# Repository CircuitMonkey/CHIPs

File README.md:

# CHIPs (aka CHIPz)

CHIPz modules are sub-circuits cooked down into a SMT module with a Cyberpunk Tech aesthetic.

The edge contacts are castelated and resemble the edge of a postage stamp.  Like similar modules on the market, CHIPs are designed to be soldered to a larger PCB board.  One advantage of the CHIPz modules is that a design can be revised or re-engineered to improve a larger design without having to redesign the whole system.  CHIPz also makes it convenient to pre-build smaller modules with common or repetive functions and use them over and over in other larger designs.

Almost all of the numbered designs were designed in EagleCAD and were intended to be sold into the hobby electronics market.  Alas, I have given up on that dream, but offer these designs for anyone who wishes to use them or just study the things I have made over the years. My current and future designs are now made with KiCAD.

I still design CHIPz modules and other things, but not for the purpose of manufacturing or selling.  I use the modules in my own creations and wish to share those things for anyone who has a similar need or wishes to simply understand the workings of these things.

If you wish to simply make a module, you can generally upload the Eagle BRD or KiCAD_PCB file directly to [OSH Park PCB](https://OSHPark.com) for preview and fabrication.

Everyting here is open source with minimal (if at all) license requirements.  Copy, mash-up and use to your hearts content.

## NOTE
New designs will be placed in a sub-directory, like [Synth] is.  Older designs will be moved eventually into a sub-folder but for now will dominate the file listing you see.

Enjoy,

Mark Koch  (Circuit Monkey)

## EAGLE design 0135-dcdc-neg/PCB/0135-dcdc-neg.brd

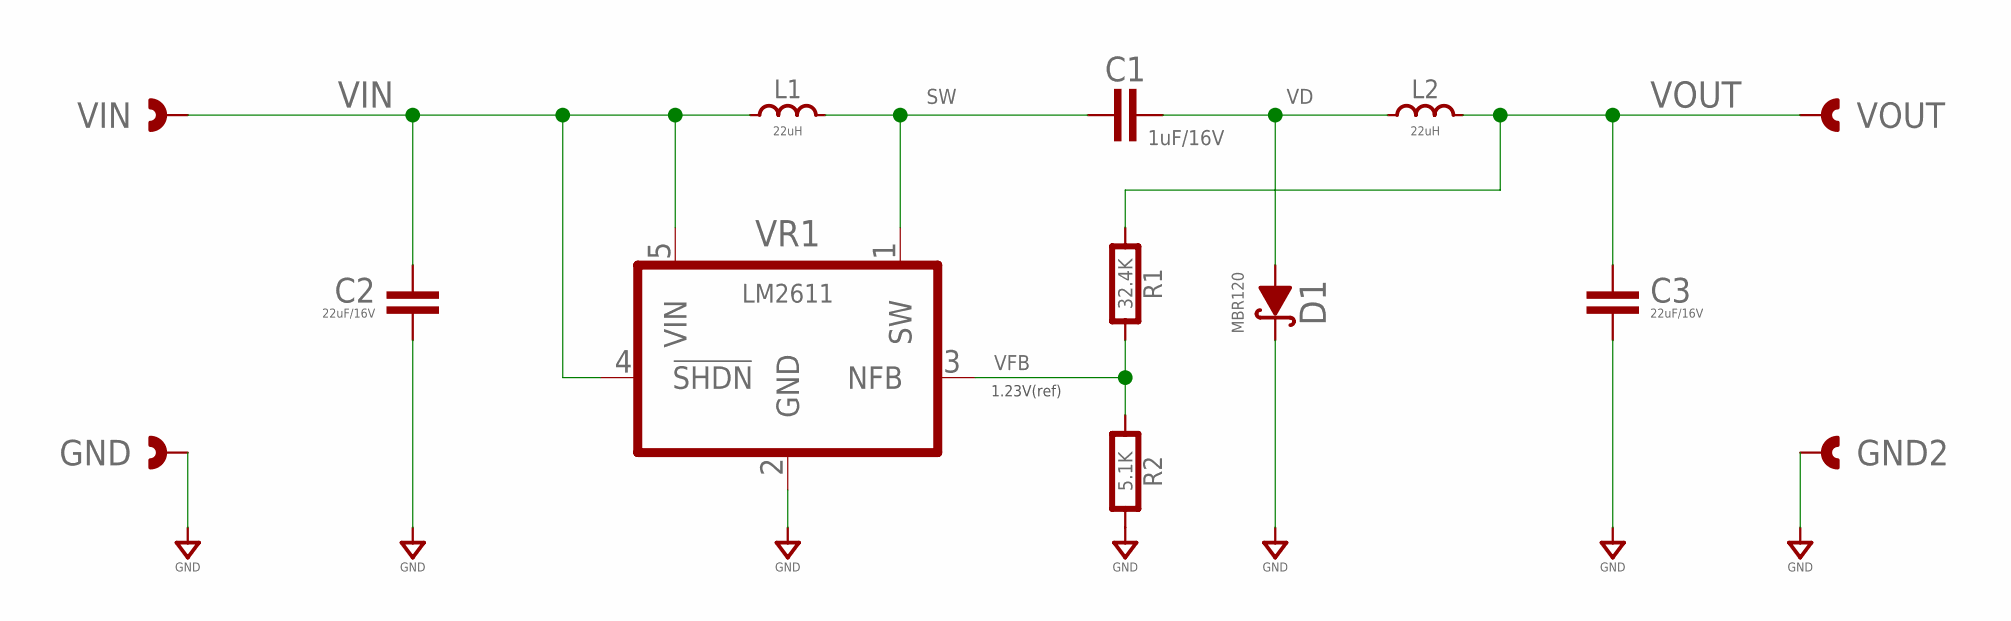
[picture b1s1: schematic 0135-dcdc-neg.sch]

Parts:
C1: 1uF/16V; 0603-CAP
C2, C3: 22uF/16V; 1210-CAP
D1: MBR120; SOD-123
GND, GND2: CAST-01X12.00MM; CAST01-2.00MM
L1, L2: 22uH; IND-MU8400
R1: 32.4K; 0603-RES
R2: 5.1K; 0603-RES
VIN: CAST-01X12.00MM; CAST01-2.00MM
VOUT: CAST-01X12.00MM; CAST01-2.00MM
VR1: LM2611; SOT-23-5

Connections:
GND: C2.2, C3.2, D1.K, GND.1, GND.P$1, GND.P$2, GND2.1, GND2.P$1, GND2.P$2, R2.2, VR1.2 (GND)
SW: C1.1, L1.1, VR1.1 (SW)
VD: C1.2, D1.A, L2.2
VFB: R1.2, R2.1, VR1.3 (NFB)
VIN: C2.1, L1.2, VIN.1, VIN.P$1, VIN.P$2, VR1.4 (!SHDN), VR1.5 (VIN)
VOUT: C3.1, L2.1, R1.1, VOUT.1, VOUT.P$1, VOUT.P$2

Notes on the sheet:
1.23V(ref)

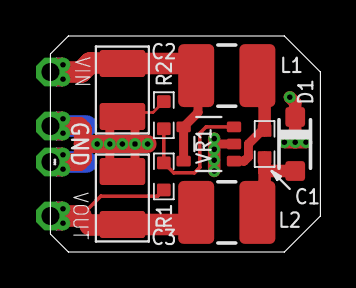
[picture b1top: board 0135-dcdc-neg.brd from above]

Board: 2 copper layers, 15.0 x 12.0 mm, 13 parts (0 on the bottom side), 6 nets.

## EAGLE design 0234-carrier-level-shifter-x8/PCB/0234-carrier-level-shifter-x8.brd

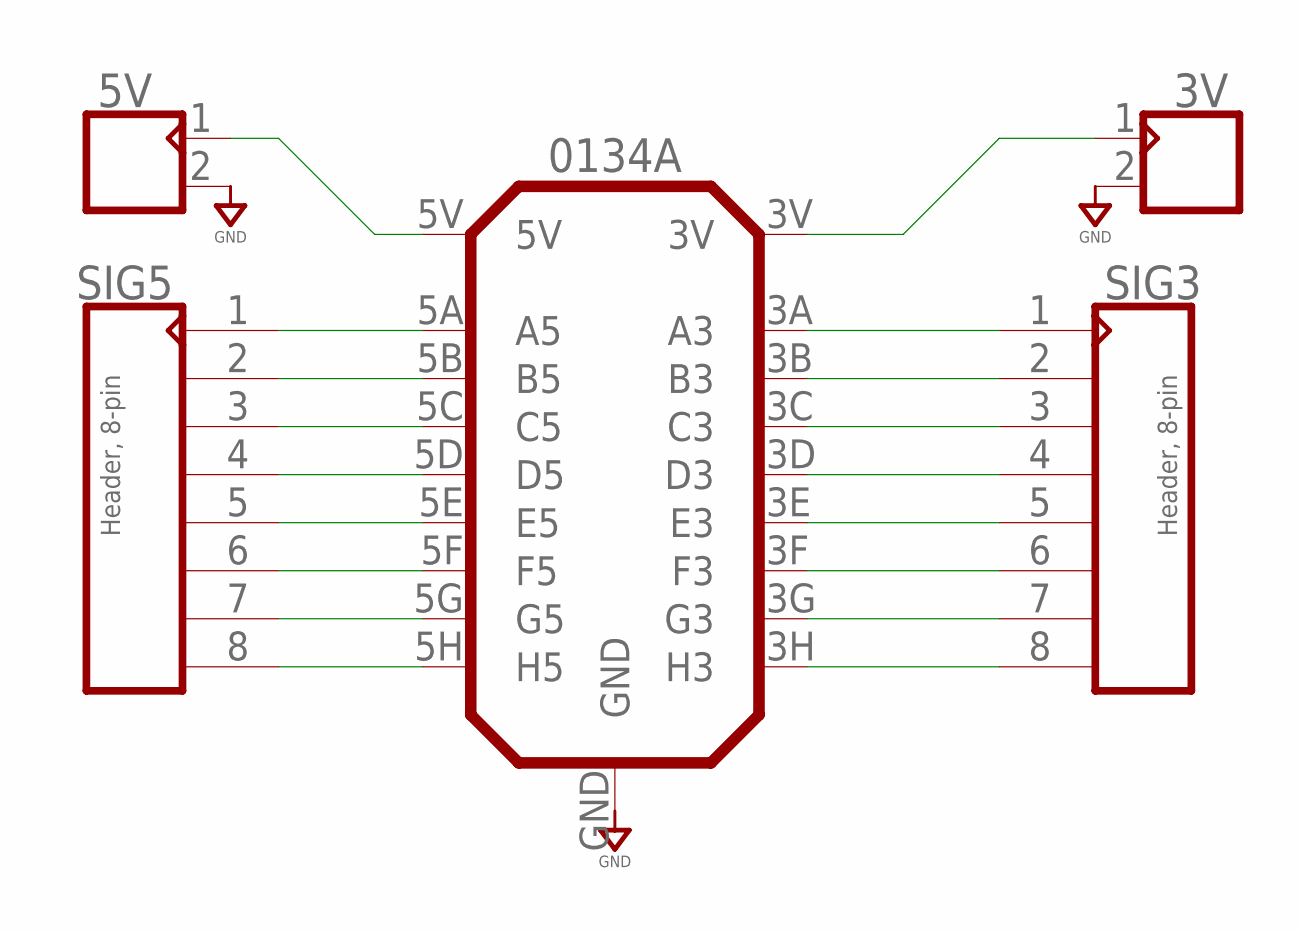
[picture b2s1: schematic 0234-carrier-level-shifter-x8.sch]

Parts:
3V, 5V: CON_02X1-2.54MM-THD-VT; MA02X1-VT-THD
0134A: 0134REV_A; 0134A
SIG3, SIG5: Header, 8-pin; MA08X1-VT-THD

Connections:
GND: 3V.2, 5V.2, 0134A.GND
unnamed: 5V.1, 0134A.5V
unnamed: 3V.1, 0134A.3V
unnamed: 0134A.5F (F5), SIG5.6
unnamed: 0134A.5E (E5), SIG5.5
unnamed: 0134A.5D (D5), SIG5.4
unnamed: 0134A.5C (C5), SIG5.3
unnamed: 0134A.5B (B5), SIG5.2
unnamed: 0134A.5A (A5), SIG5.1
unnamed: 0134A.5G (G5), SIG5.7
unnamed: 0134A.5H (H5), SIG5.8
unnamed: 0134A.3F (F3), SIG3.6
unnamed: 0134A.3E (E3), SIG3.5
unnamed: 0134A.3D (D3), SIG3.4
unnamed: 0134A.3C (C3), SIG3.3
unnamed: 0134A.3B (B3), SIG3.2
unnamed: 0134A.3A (A3), SIG3.1
unnamed: 0134A.3G (G3), SIG3.7
unnamed: 0134A.3H (H3), SIG3.8

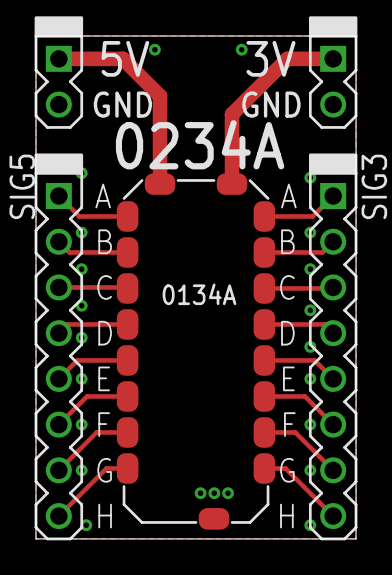
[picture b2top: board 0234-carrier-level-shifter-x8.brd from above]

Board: 2 copper layers, 17.8 x 27.9 mm, 5 parts (0 on the bottom side), 19 nets.

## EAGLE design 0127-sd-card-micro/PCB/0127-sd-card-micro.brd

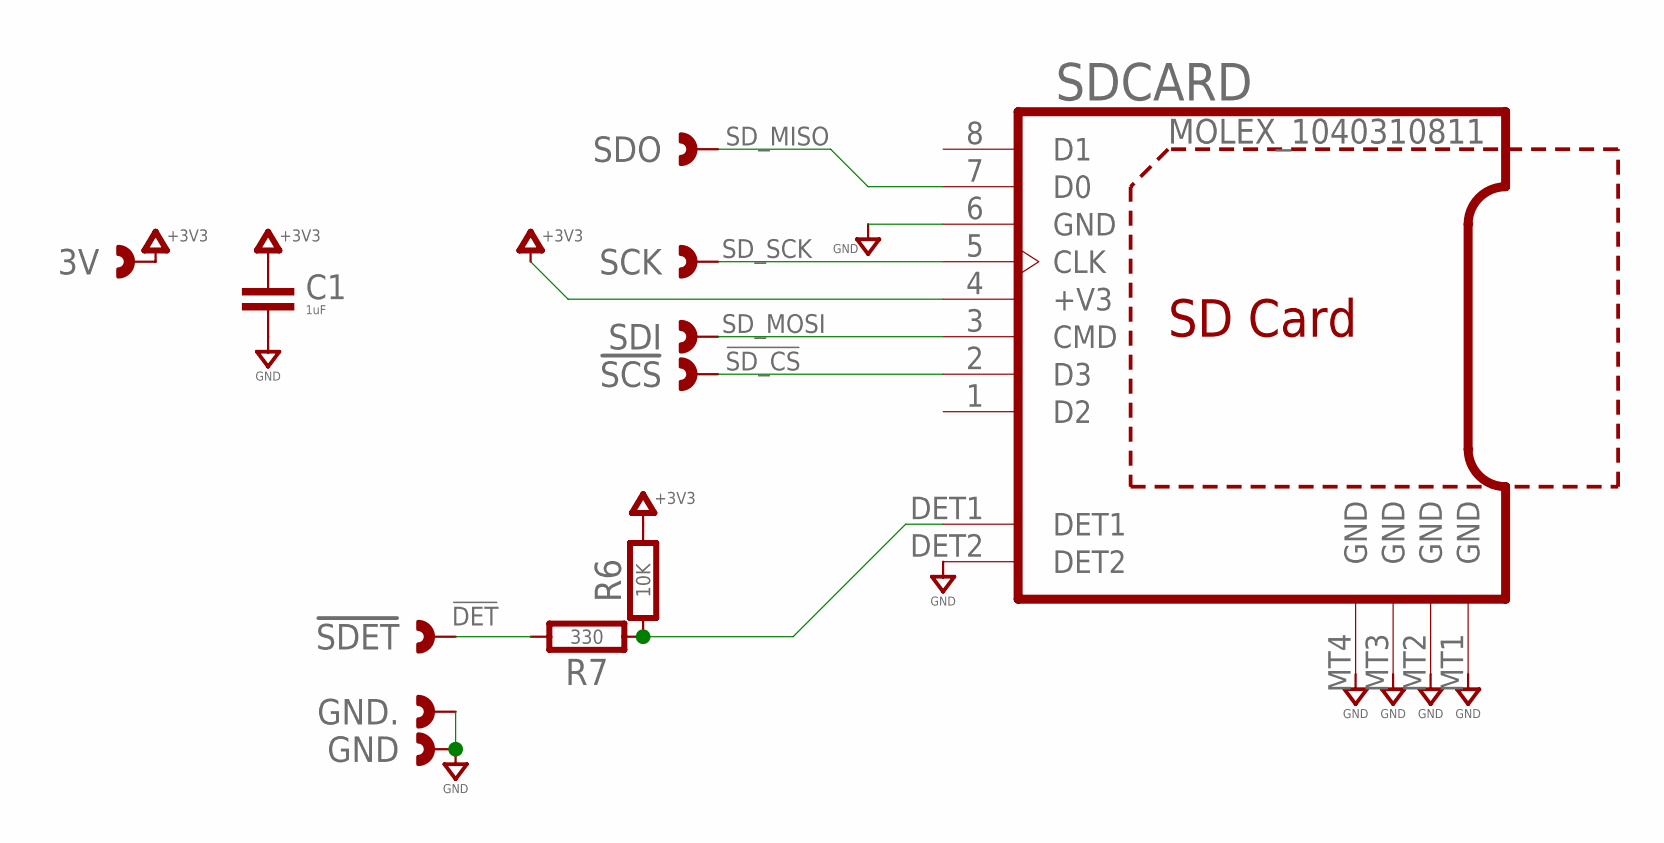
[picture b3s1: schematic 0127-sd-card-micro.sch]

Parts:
3V: CAST-01X12.00MM; CAST01-2.00MM
!SCS: CAST-01X12.00MM; CAST01-2.00MM
!SDET: CAST-01X12.00MM; CAST01-2.00MM
C1: 1uF; 0603-CAP
GND, GND.: CAST-01X12.00MM; CAST01-2.00MM
R6: 10K; 0603-RES
R7: 330; 0603-RES
SCK: CAST-01X12.00MM; CAST01-2.00MM
SDCARD: MOLEX_1040310811; MOLEX_1040310811_USD
SDI: CAST-01X12.00MM; CAST01-2.00MM
SDO: CAST-01X12.00MM; CAST01-2.00MM

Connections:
!DET: !SDET.1, !SDET.P$1, !SDET.P$2, R7.2
!SD_CS: !SCS.1, !SCS.P$1, !SCS.P$2, SDCARD.2 (D3)
!SD_DET: R6.1, R7.1, SDCARD.DET1
+3V3: 3V.1, 3V.P$1, 3V.P$2, C1.1, R6.2, SDCARD.4 (+V3)
GND: C1.2, GND.1, GND.P$1, GND.P$2, GND..1, GND..P$1, GND..P$2, SDCARD.6 (GND), SDCARD.DET2, SDCARD.MT1 (GND), SDCARD.MT2 (GND), SDCARD.MT3 (GND), SDCARD.MT4 (GND)
SD_MISO: SDCARD.7 (D0), SDO.1, SDO.P$1, SDO.P$2
SD_MOSI: SDCARD.3 (CMD), SDI.1, SDI.P$1, SDI.P$2
SD_SCK: SCK.1, SCK.P$1, SCK.P$2, SDCARD.5 (CLK)

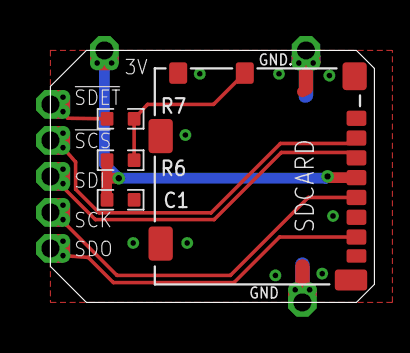
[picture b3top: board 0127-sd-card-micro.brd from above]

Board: 2 copper layers, 18.0 x 14.0 mm, 12 parts (0 on the bottom side), 8 nets.

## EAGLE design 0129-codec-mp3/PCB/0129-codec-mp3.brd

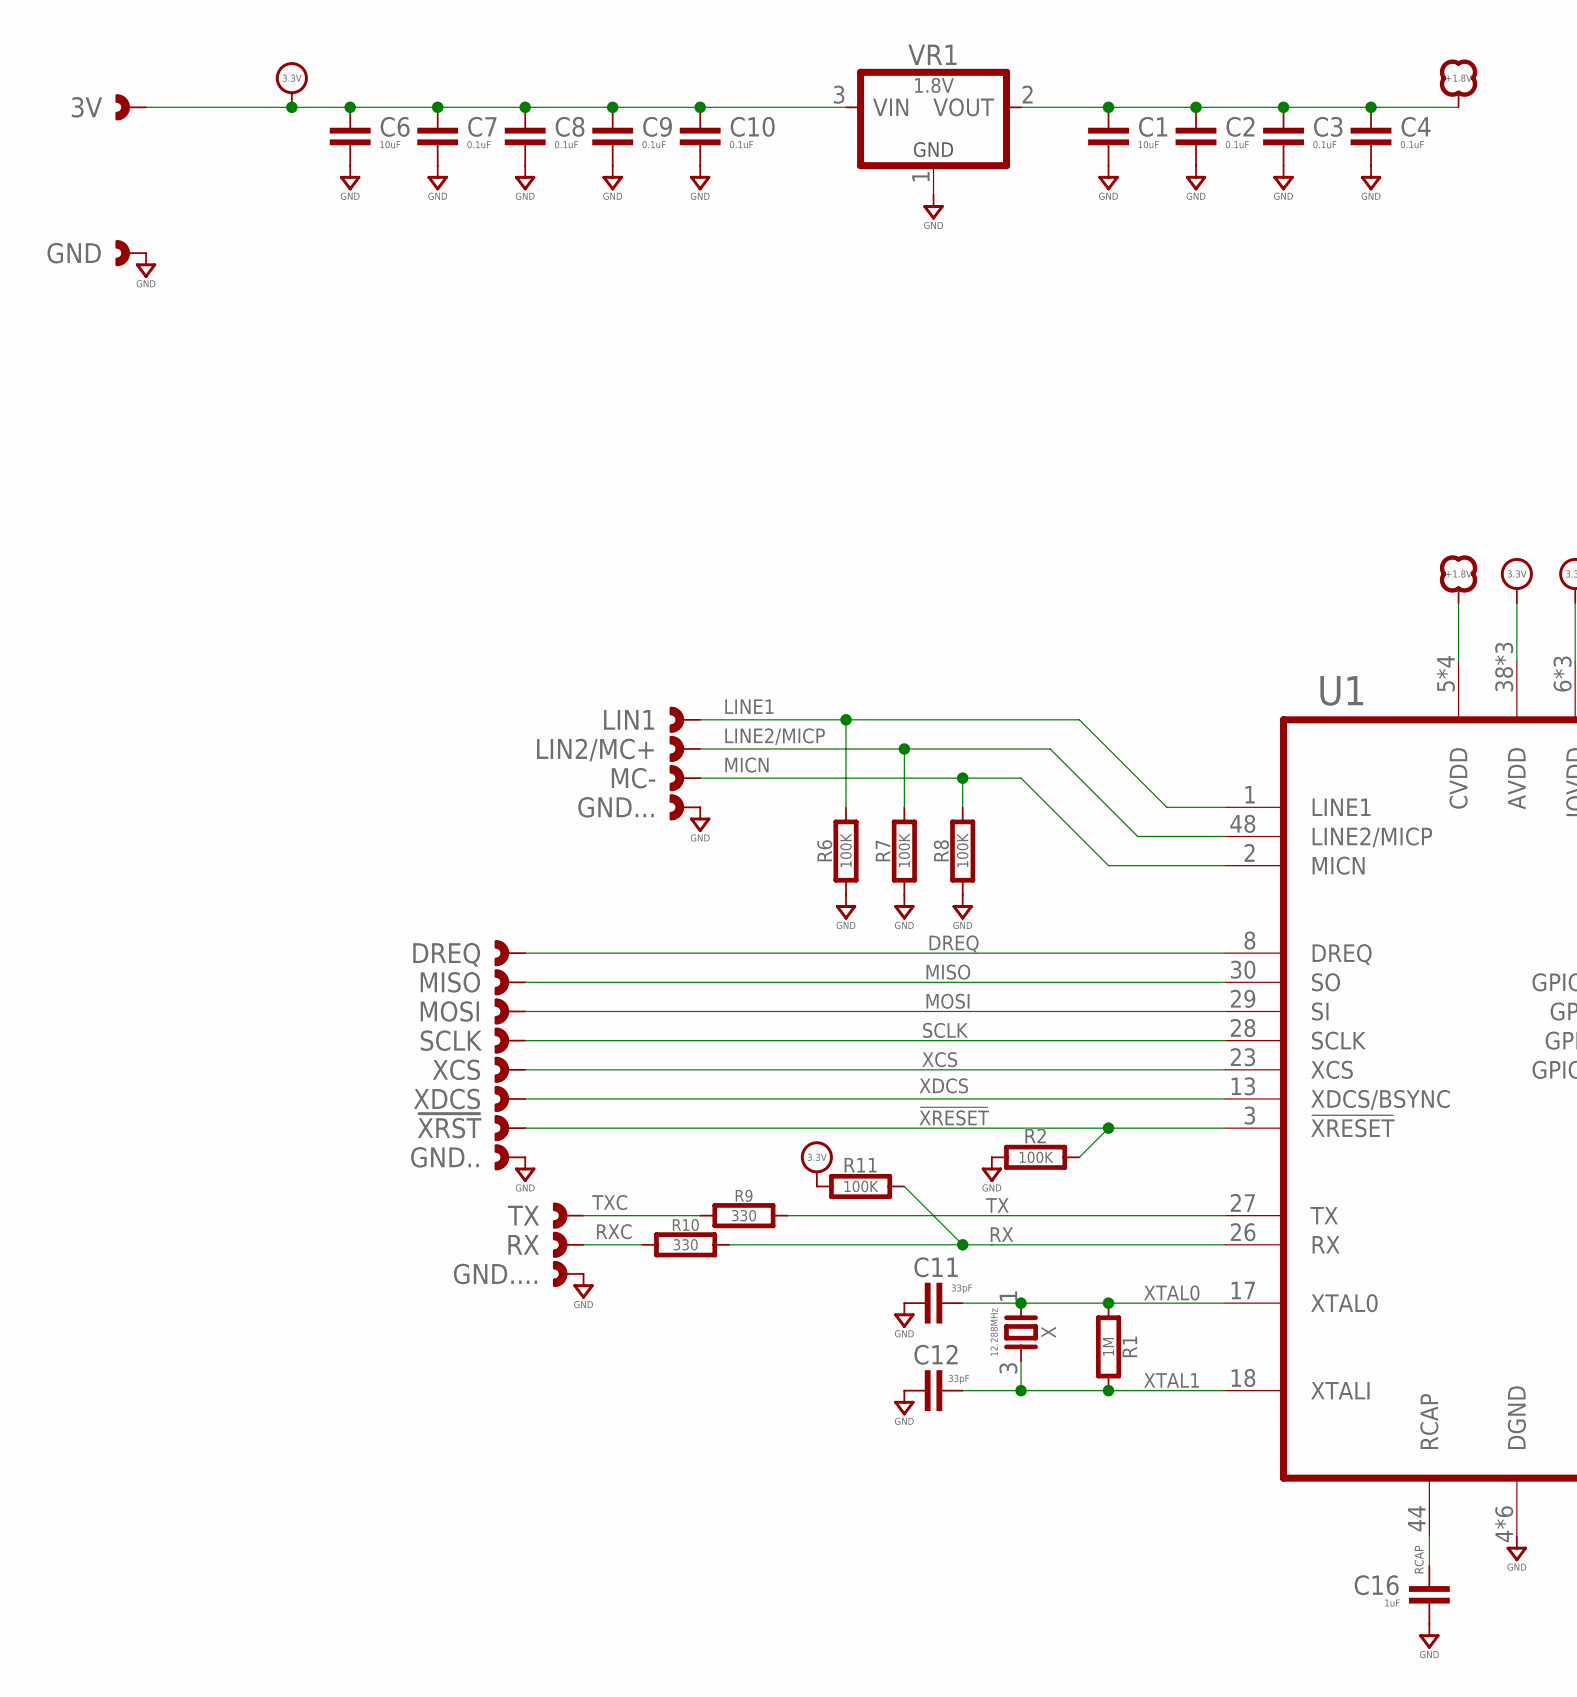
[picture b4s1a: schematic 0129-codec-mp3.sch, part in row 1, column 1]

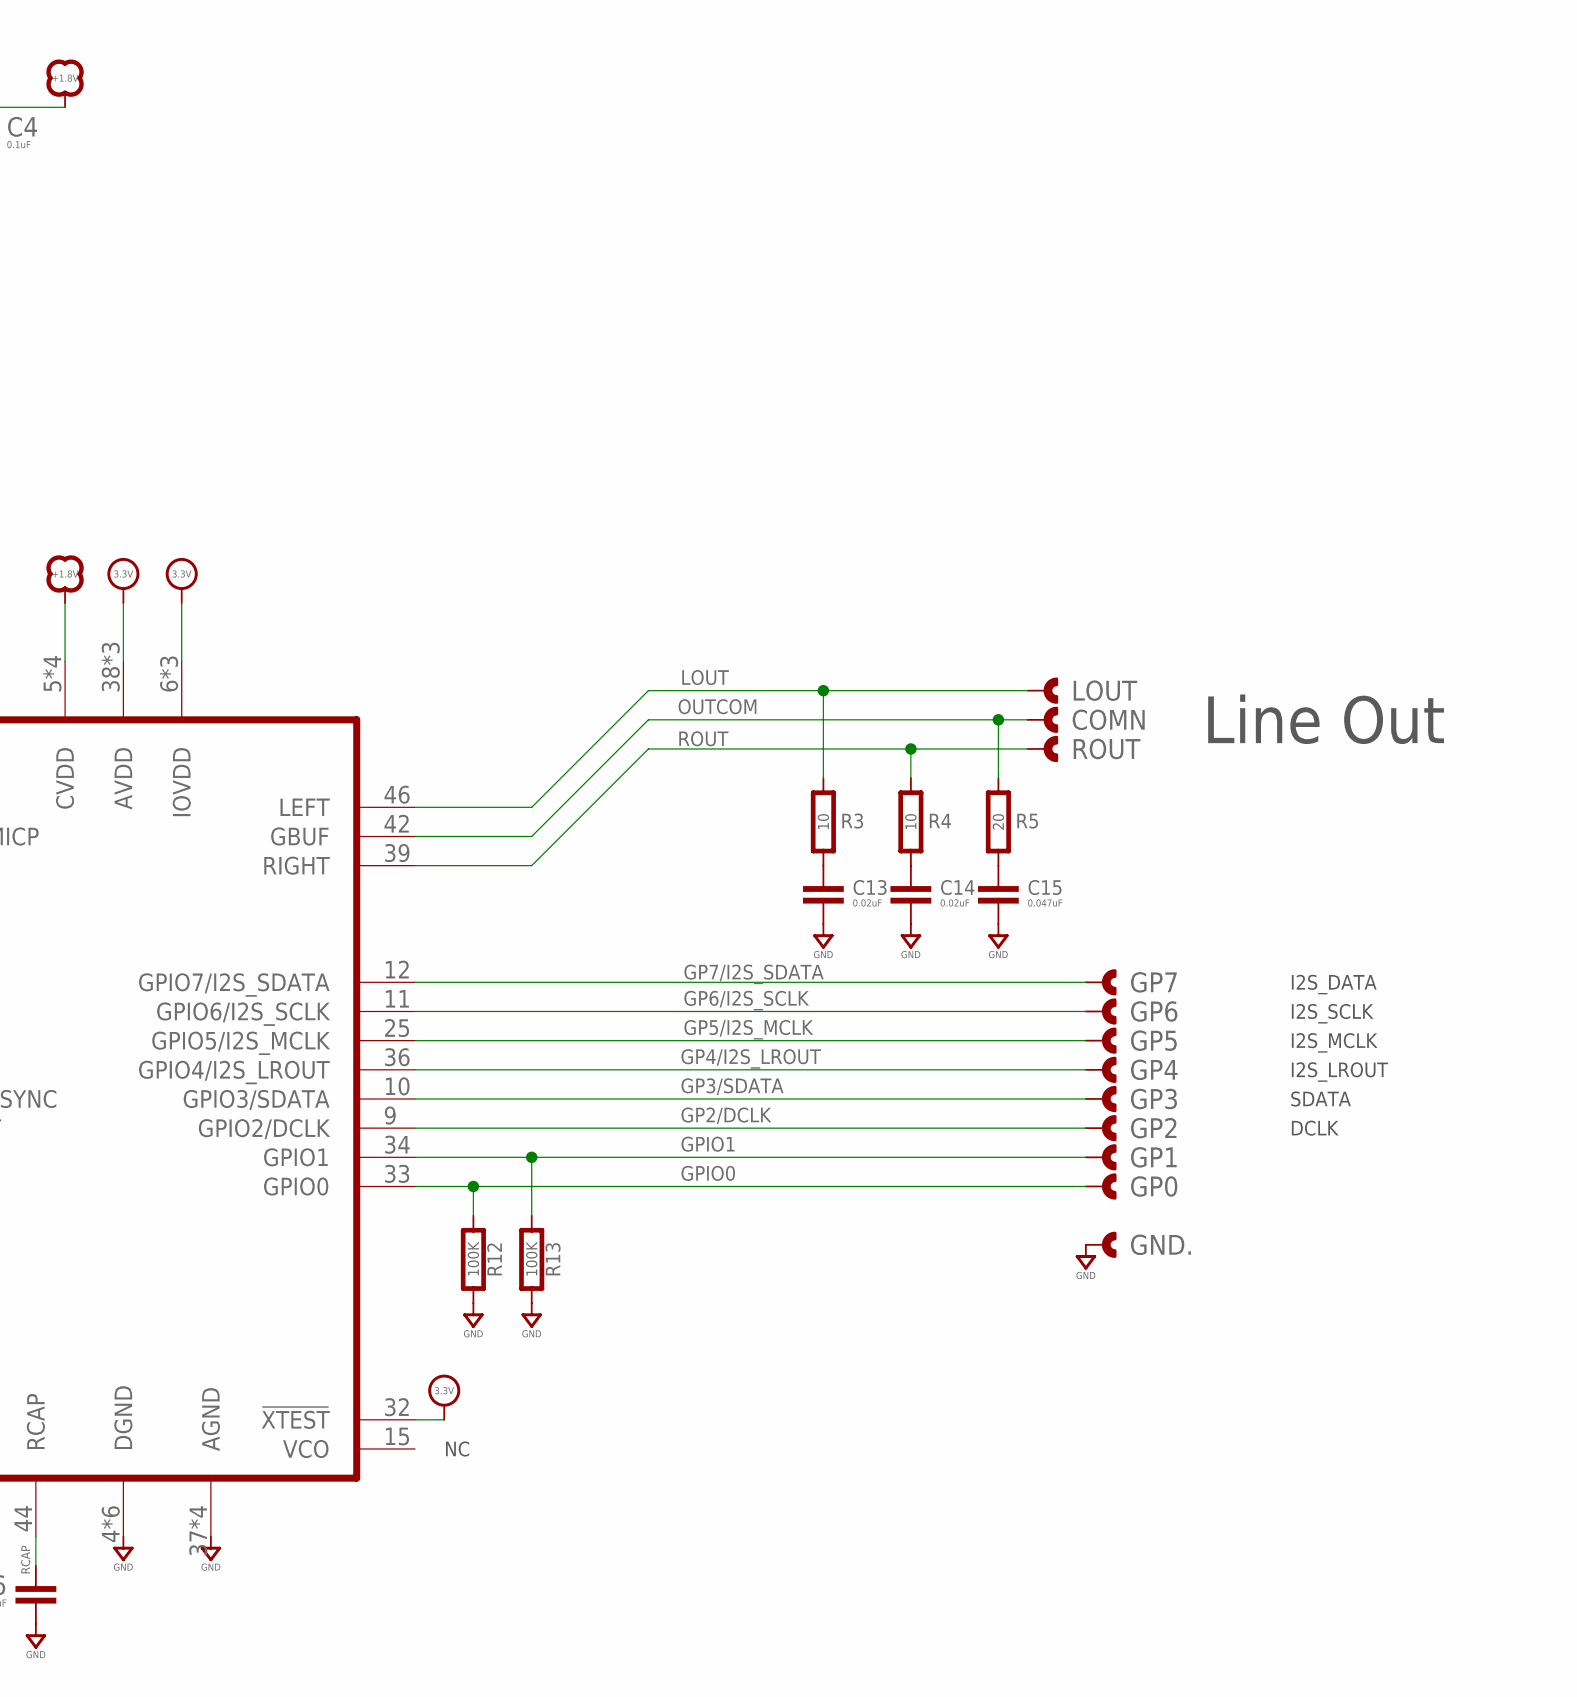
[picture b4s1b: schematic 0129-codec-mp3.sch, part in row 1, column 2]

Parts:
3V: CAST-01X12.00MM; CAST01-2.00MM
!XRST: CAST-01X12.00MM; CAST01-2.00MM
C1, C6: 10uF; 0603-CAP
C2, C3, C4, C7, C8, C9, C10: 0.1uF; 0603-CAP
C11, C12: 33pF; 0603-CAP
C13, C14: 0.02uF; 0603-CAP
C15: 0.047uF; 0603-CAP
C16: 1uF; 0603-CAP
COMN: CAST-01X12.00MM; CAST01-2.00MM
DREQ: CAST-01X12.00MM; CAST01-2.00MM
GND, GND., GND.., GND..., GND....: CAST-01X12.00MM; CAST01-2.00MM
GP0, GP1, GP2, GP3, GP4, GP5, GP6, GP7: CAST-01X12.00MM; CAST01-2.00MM
LIN1, LIN2/MC+: CAST-01X12.00MM; CAST01-2.00MM
LOUT: CAST-01X12.00MM; CAST01-2.00MM
MC-: CAST-01X12.00MM; CAST01-2.00MM
MISO: CAST-01X12.00MM; CAST01-2.00MM
MOSI: CAST-01X12.00MM; CAST01-2.00MM
R1: 1M; 0603-RES
R2, R6, R7, R8, R11, R12, R13: 100K; 0603-RES
R3, R4: 10; 0603-RES
R5: 20; 0603-RES
R9, R10: 330; 0603-RES
ROUT: CAST-01X12.00MM; CAST01-2.00MM
RX: CAST-01X12.00MM; CAST01-2.00MM
SCLK: CAST-01X12.00MM; CAST01-2.00MM
TX: CAST-01X12.00MM; CAST01-2.00MM
U1: CODEC-VS1053; LQFP-48
VR1: 1.8V; SOT-23
X: 12.288MHz; 32X25
XCS: CAST-01X12.00MM; CAST01-2.00MM
XDCS: CAST-01X12.00MM; CAST01-2.00MM

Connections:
!XRESET: !XRST.1, !XRST.P$1, !XRST.P$2, R2.2, U1.3 (!XRESET)
+1.8V: C1.1, C2.1, C3.1, C4.1, U1.5 (CVDD), U1.7 (CVDD), U1.24 (CVDD), U1.31 (CVDD), VR1.2 (VOUT)
+3.3V: 3V.1, 3V.P$1, 3V.P$2, C6.1, C7.1, C8.1, C9.1, C10.1, R11.1, U1.6 (IOVDD), U1.14 (IOVDD), U1.19 (IOVDD), U1.32 (!XTEST), U1.38 (AVDD), U1.43 (AVDD), U1.45 (AVDD), VR1.3 (VIN)
DREQ: DREQ.1, DREQ.P$1, DREQ.P$2, U1.8 (DREQ)
GND: C1.2, C2.2, C3.2, C4.2, C6.2, C7.2, C8.2, C9.2, C10.2, C11.1, C12.1, C13.2, C14.2, C15.2, C16.2, GND.1, GND.P$1, GND.P$2, GND..1, GND..P$1, GND..P$2, GND...1, GND...P$1, GND...P$2, GND....1, GND....P$1, GND....P$2, GND.....1, GND.....P$1, GND.....P$2, R2.1, R6.1, R7.1, R8.1, R12.2, R13.2, U1.4 (DGND), U1.16 (DGND), U1.20 (DGND), U1.21 (DGND), U1.22 (DGND), U1.35 (DGND), U1.37 (AGND), U1.40 (AGND), U1.41 (AGND), U1.47 (AGND), VR1.1 (GND)
GP2/DCLK: GP2.1, GP2.P$1, GP2.P$2, U1.9 (GPIO2/DCLK)
GP3/SDATA: GP3.1, GP3.P$1, GP3.P$2, U1.10 (GPIO3/SDATA)
GP4/I2S_LROUT: GP4.1, GP4.P$1, GP4.P$2, U1.36 (GPIO4/I2S_LROUT)
GP5/I2S_MCLK: GP5.1, GP5.P$1, GP5.P$2, U1.25 (GPIO5/I2S_MCLK)
GP6/I2S_SCLK: GP6.1, GP6.P$1, GP6.P$2, U1.11 (GPIO6/I2S_SCLK)
GP7/I2S_SDATA: GP7.1, GP7.P$1, GP7.P$2, U1.12 (GPIO7/I2S_SDATA)
GPIO0: GP0.1, GP0.P$1, GP0.P$2, R12.1, U1.33 (GPIO0)
GPIO1: GP1.1, GP1.P$1, GP1.P$2, R13.1, U1.34 (GPIO1)
LINE1: LIN1.1, LIN1.P$1, LIN1.P$2, R6.2, U1.1 (LINE1)
LINE2/MICP: LIN2/MC+.1, LIN2/MC+.P$1, LIN2/MC+.P$2, R7.2, U1.48 (LINE2/MICP)
LOUT: LOUT.1, LOUT.P$1, LOUT.P$2, R3.1, U1.46 (LEFT)
MICN: MC-.1, MC-.P$1, MC-.P$2, R8.2, U1.2 (MICN)
MISO: MISO.1, MISO.P$1, MISO.P$2, U1.30 (SO)
MOSI: MOSI.1, MOSI.P$1, MOSI.P$2, U1.29 (SI)
unnamed: C13.1, R3.2
unnamed: C14.1, R4.2
unnamed: C15.1, R5.2
OUTCOM: COMN.1, COMN.P$1, COMN.P$2, R5.1, U1.42 (GBUF)
RCAP: C16.1, U1.44 (RCAP)
ROUT: R4.1, ROUT.1, ROUT.P$1, ROUT.P$2, U1.39 (RIGHT)
RX: R10.2, R11.2, U1.26 (RX)
RXC: R10.1, RX.1, RX.P$1, RX.P$2
SCLK: SCLK.1, SCLK.P$1, SCLK.P$2, U1.28 (SCLK)
TX: R9.2, U1.27 (TX)
TXC: R9.1, TX.1, TX.P$1, TX.P$2
XCS: U1.23 (XCS), XCS.1, XCS.P$1, XCS.P$2
XDCS: U1.13 (XDCS/BSYNC), XDCS.1, XDCS.P$1, XDCS.P$2
XTAL0: C11.2, R1.1, U1.17 (XTAL0), X.1
XTAL1: C12.2, R1.2, U1.18 (XTALI), X.3

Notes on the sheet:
Line Out
I2S_DATA
I2S_SCLK
I2S_MCLK
I2S_LROUT
SDATA
DCLK

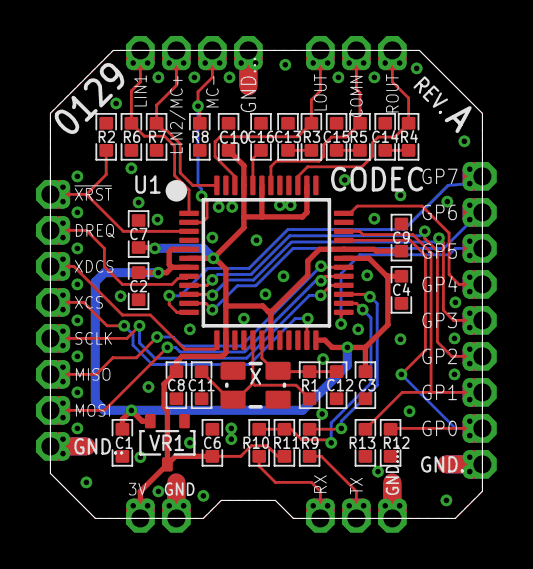
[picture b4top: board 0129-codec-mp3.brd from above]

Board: 2 copper layers, 24.0 x 26.0 mm, 60 parts (0 on the bottom side), 34 nets.

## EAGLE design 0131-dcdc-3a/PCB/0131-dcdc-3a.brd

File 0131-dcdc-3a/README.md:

# Circuit Monkey CHIPs &#35;0131 -- DCDC Converter 1.8V-5V@2A-3A

## Description
DC Buck Voltage converter.  Default config is 5V at 3Amps but capable of 1.8V to 5V range (using specific feedback resistor values) and current range of 2A - 3A max using alternative chip part numbers.

Features TSOP26 size package.   Our 0121A model is this same circuit but uses the SOT563 (smaller) package.  Note: Pinout is reversed for 0121 model.

## Images

## Technical Details
* **Dimensions:** 11.5mm wide x 9mm tall  x 0.8mm PCB thickness
* **Pad Style:** Castellated Pin Edges allow easy surface mounting as well as hand wiring
* **Pad Pitch:** Minimum Pad Pitch is 2.0mm
* **Chip, 3A:** Diodes Inc. [AP62300 DCDC Converter](https://www.diodes.com/assets/Datasheets/AP62300_AP62301_AP62300T.pdf)
* **Chip, 2A:** Diodes Inc. [AP62200 DCDC Converter](https://www.diodes.com/assets/Datasheets/AP62200_AP62201_AP62200T.pdf)

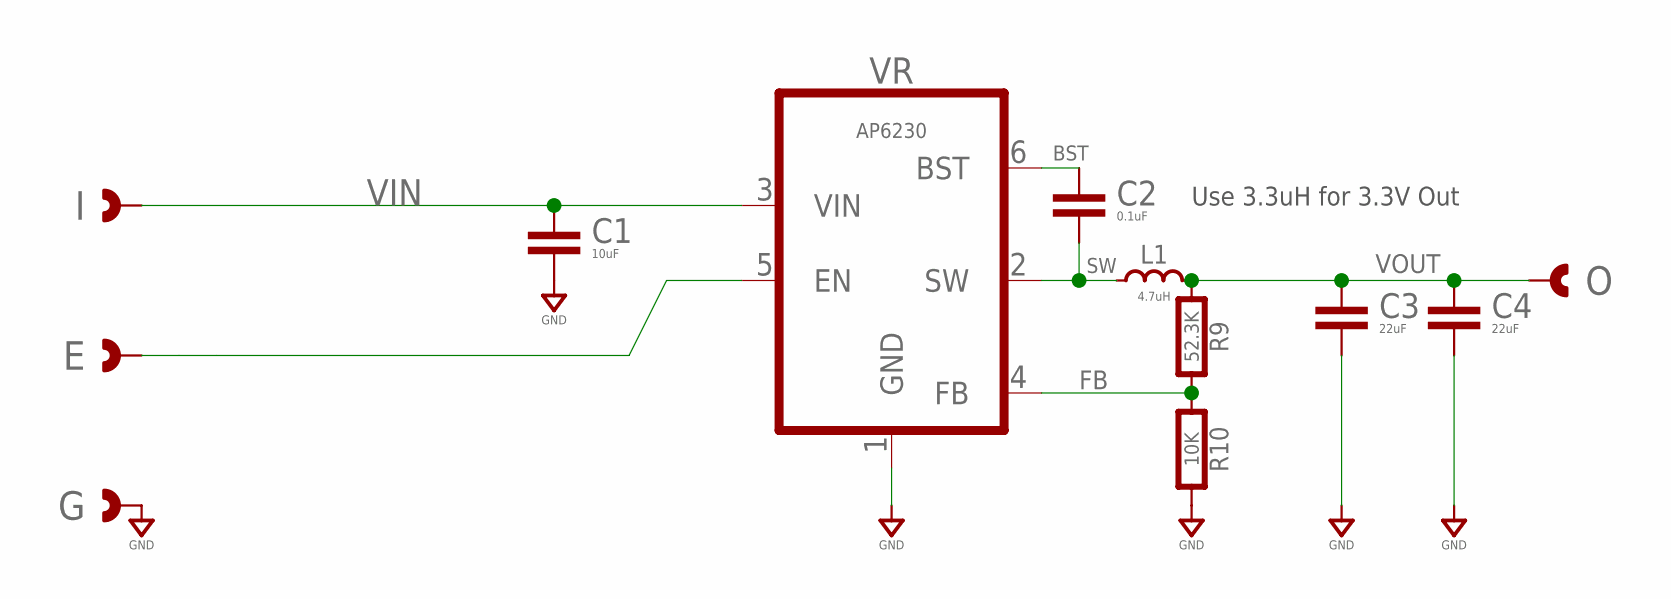
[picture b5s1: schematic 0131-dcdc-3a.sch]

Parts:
C1: 10uF; 0603-CAP
C2: 0.1uF; 0603-CAP
C3, C4: 22uF; 0603-CAP
E: CAST-01X12.00MM; CAST01-2.00MM
G: CAST-01X12.00MM; CAST01-2.00MM
I: CAST-01X12.00MM; CAST01-2.00MM
L1: 4.7uH; IND-SRN5040; MPN SRN5040-3R3M
O: CAST-01X12.00MM; CAST01-2.00MM
R9: 52.3K; 0603-RES
R10: 10K; 0603-RES
VR: AP6230; TSOT26

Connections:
BST: C2.1, VR.6 (BST)
FB: R9.2, R10.1, VR.4 (FB)
GND: C1.2, C3.2, C4.2, G.1, G.P$1, G.P$2, R10.2, VR.1 (GND)
unnamed: E.1, E.P$1, E.P$2, VR.5 (EN)
SW: C2.2, L1.2, VR.2 (SW)
VIN: C1.1, I.1, I.P$1, I.P$2, VR.3 (VIN)
VOUT: C3.1, C4.1, L1.1, O.1, O.P$1, O.P$2, R9.1

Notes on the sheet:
Use 3.3uH for 3.3V Out

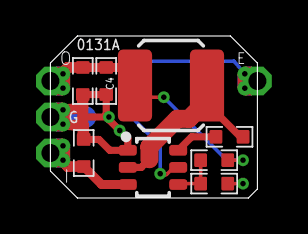
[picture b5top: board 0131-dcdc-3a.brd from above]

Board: 2 copper layers, 11.5 x 9.0 mm, 12 parts (0 on the bottom side), 7 nets.

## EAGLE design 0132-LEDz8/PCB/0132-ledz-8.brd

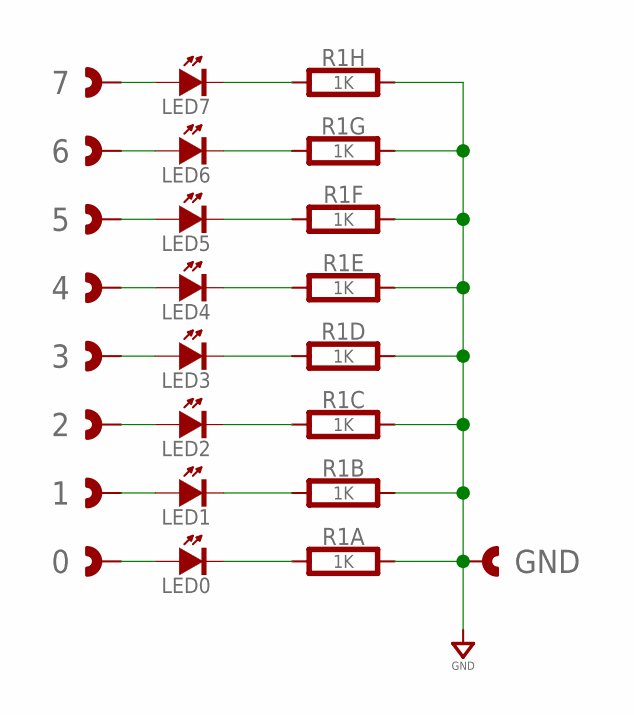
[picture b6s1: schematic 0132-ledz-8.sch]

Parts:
0, 1, 2, 3, 4, 5, 6, 7: CAST-01X12.00MM; CAST01-2.00MM
GND: CAST-01X12.00MM; CAST01-2.00MM
LED0, LED1, LED2, LED3, LED4, LED5, LED6, LED7: SMT0603; SMD_0603
R1: 1K; RESNET_0402_X8

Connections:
GND: GND.1, GND.P$1, GND.P$2, R1.1, R1.2 (1), R1.3 (1), R1.4 (1), R1.5 (1), R1.6 (1), R1.7 (1), R1.8 (1)
LED0: 0.1, 0.P$1, 0.P$2, LED0.A
LED1: 1.1, 1.P$1, 1.P$2, LED1.A
LED2: 2.1, 2.P$1, 2.P$2, LED2.A
LED3: 3.1, 3.P$1, 3.P$2, LED3.A
LED4: 4.1, 4.P$1, 4.P$2, LED4.A
LED5: 5.1, 5.P$1, 5.P$2, LED5.A
LED6: 6.1, 6.P$1, 6.P$2, LED6.A
LED7: 7.1, 7.P$1, 7.P$2, LED7.A
unnamed: LED0.K (C), R1.16 (2)
unnamed: LED1.K (C), R1.15 (2)
unnamed: LED2.K (C), R1.14 (2)
unnamed: LED3.K (C), R1.13 (2)
unnamed: LED4.K (C), R1.12 (2)
unnamed: LED5.K (C), R1.11 (2)
unnamed: LED6.K (C), R1.10 (2)
unnamed: LED7.K (C), R1.9 (2)

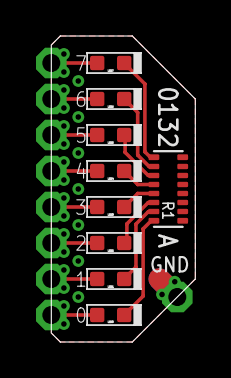
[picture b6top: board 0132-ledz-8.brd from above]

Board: 2 copper layers, 8.0 x 17.0 mm, 18 parts (0 on the bottom side), 17 nets.

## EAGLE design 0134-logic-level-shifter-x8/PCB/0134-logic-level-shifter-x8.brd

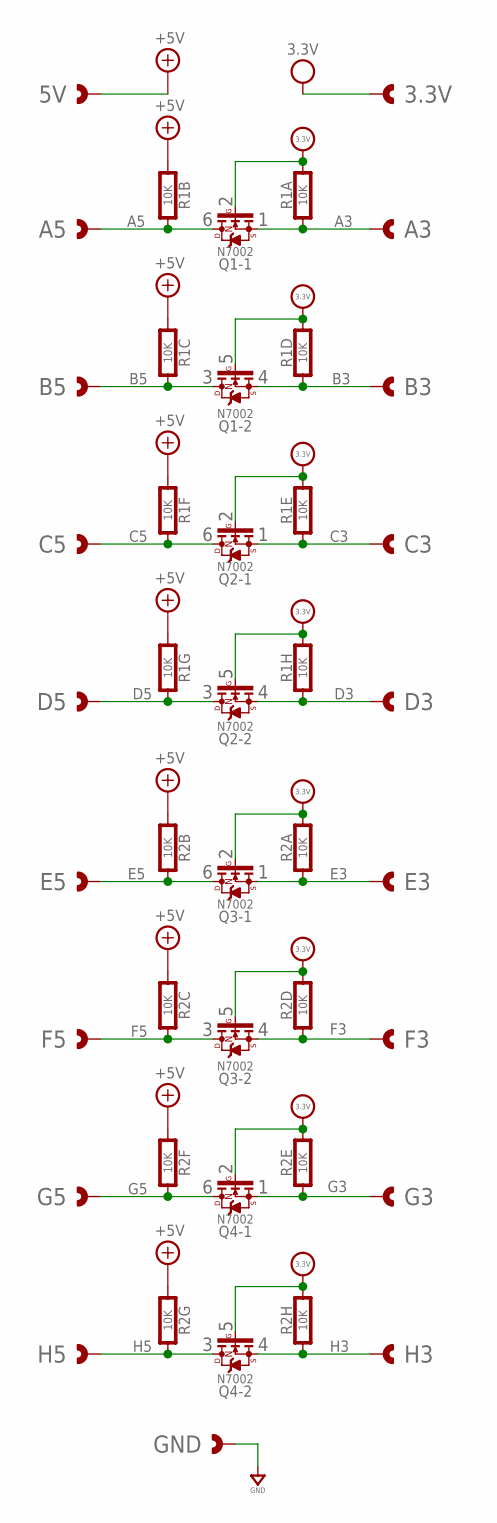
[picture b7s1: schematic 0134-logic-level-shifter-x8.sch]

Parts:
3.3V, 5V: CAST-01X12.00MM; CAST01-2.00MM
A3, A5: CAST-01X12.00MM; CAST01-2.00MM
B3, B5: CAST-01X12.00MM; CAST01-2.00MM
C3, C5: CAST-01X12.00MM; CAST01-2.00MM
D3, D5: CAST-01X12.00MM; CAST01-2.00MM
E3, E5: CAST-01X12.00MM; CAST01-2.00MM
F3, F5: CAST-01X12.00MM; CAST01-2.00MM
G3, G5: CAST-01X12.00MM; CAST01-2.00MM
GND: CAST-01X12.00MM; CAST01-2.00MM
H3, H5: CAST-01X12.00MM; CAST01-2.00MM
Q1, Q2, Q3, Q4: N7002; SOT-563
R1, R2: 10K; RESNET_0402_X8

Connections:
+3.3V: 3.3V.1, 3.3V.P$1, 3.3V.P$2, Q1.2 (G), Q1.5 (G), Q2.2 (G), Q2.5 (G), Q3.2 (G), Q3.5 (G), Q4.2 (G), Q4.5 (G), R1.1, R1.4 (1), R1.5 (1), R1.8 (1), R2.1, R2.4 (1), R2.5 (1), R2.8 (1)
+5V: 5V.1, 5V.P$1, 5V.P$2, R1.10 (2), R1.11 (2), R1.14 (2), R1.15 (2), R2.10 (2), R2.11 (2), R2.14 (2), R2.15 (2)
A3: A3.1, A3.P$1, A3.P$2, Q1.1 (S), R1.16 (2)
A5: A5.1, A5.P$1, A5.P$2, Q1.6 (D), R1.2 (1)
B3: B3.1, B3.P$1, B3.P$2, Q1.4 (S), R1.13 (2)
B5: B5.1, B5.P$1, B5.P$2, Q1.3 (D), R1.3 (1)
C3: C3.1, C3.P$1, C3.P$2, Q2.1 (S), R1.12 (2)
C5: C5.1, C5.P$1, C5.P$2, Q2.6 (D), R1.6 (1)
D3: D3.1, D3.P$1, D3.P$2, Q2.4 (S), R1.9 (2)
D5: D5.1, D5.P$1, D5.P$2, Q2.3 (D), R1.7 (1)
E3: E3.1, E3.P$1, E3.P$2, Q3.1 (S), R2.16 (2)
E5: E5.1, E5.P$1, E5.P$2, Q3.6 (D), R2.2 (1)
F3: F3.1, F3.P$1, F3.P$2, Q3.4 (S), R2.13 (2)
F5: F5.1, F5.P$1, F5.P$2, Q3.3 (D), R2.3 (1)
G3: G3.1, G3.P$1, G3.P$2, Q4.1 (S), R2.12 (2)
G5: G5.1, G5.P$1, G5.P$2, Q4.6 (D), R2.6 (1)
GND: GND.1, GND.P$1, GND.P$2
H3: H3.1, H3.P$1, H3.P$2, Q4.4 (S), R2.9 (2)
H5: H5.1, H5.P$1, H5.P$2, Q4.3 (D), R2.7 (1)

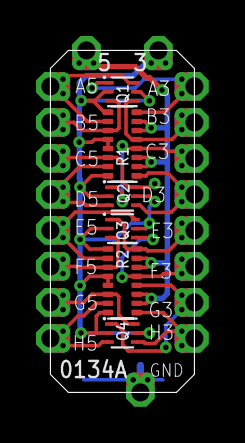
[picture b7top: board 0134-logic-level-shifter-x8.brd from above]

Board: 2 copper layers, 8.0 x 19.0 mm, 25 parts (0 on the bottom side), 19 nets.

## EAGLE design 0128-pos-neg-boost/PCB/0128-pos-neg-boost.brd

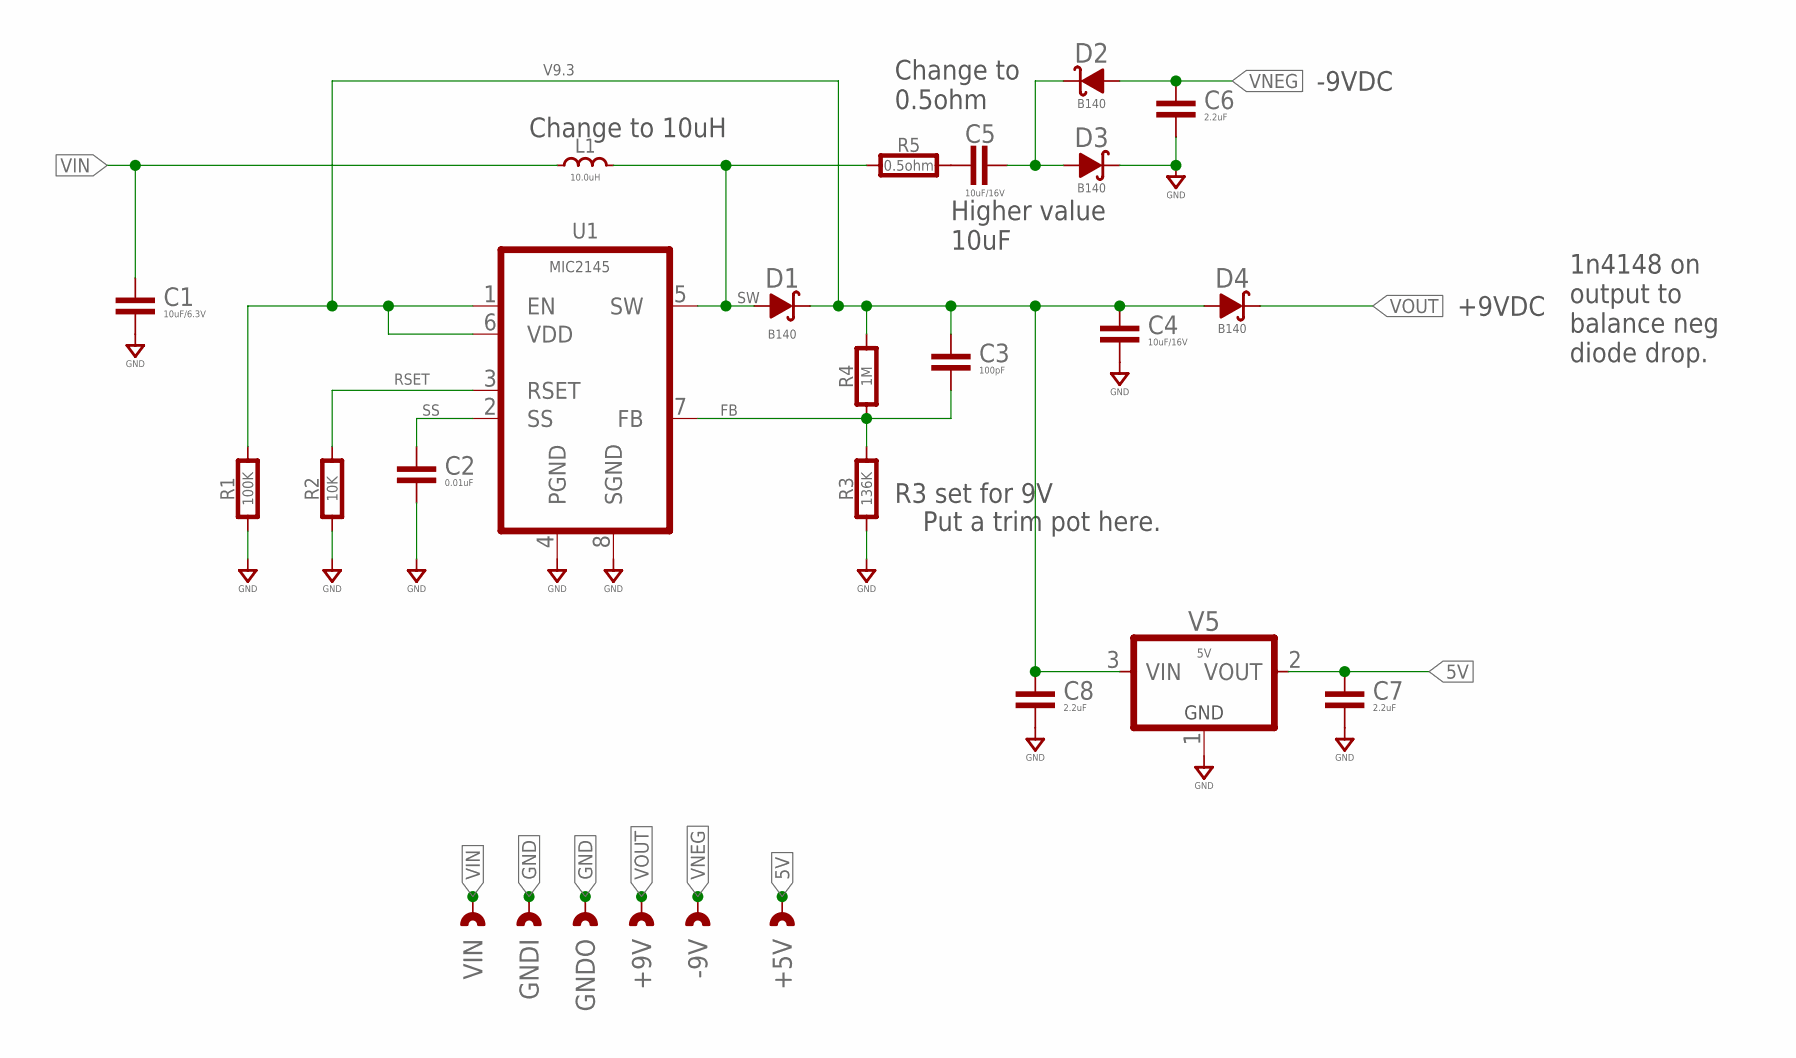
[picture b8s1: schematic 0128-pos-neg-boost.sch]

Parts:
+5V, +9V: CAST-01X12.00MM; CAST01-2.00MM
-9V: CAST-01X12.00MM; CAST01-2.00MM
C1: 10uF/6.3V; 0603-CAP
C2: 0.01uF; 0603-CAP
C3: 100pF; 0603-CAP
C4, C5: 10uF/16V; 0603-CAP
C6, C7, C8: 2.2uF; 0603-CAP
D1, D2, D3, D4: B140; SMA
GNDI: CAST-01X12.00MM; CAST01-2.00MM
GNDO: CAST-01X12.00MM; CAST01-2.00MM
L1: 10.0uH; IND-SRN5040
R1: 100K; 0603-RES
R2: 10K; 0603-RES
R3: 136K; 0603-RES
R4: 1M; 0603-RES
R5: 0.5ohm; 0603-RES
U1: MIC2145; MSOP8-0.65
V5: 5V; SOT-23
VIN: CAST-01X12.00MM; CAST01-2.00MM

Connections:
5V: +5V.1, +5V.P$1, +5V.P$2, C7.1, V5.2 (VOUT)
FB: C3.2, R3.2, R4.1, U1.7 (FB)
GND: C1.2, C2.2, C4.2, C6.2, C7.2, C8.2, D3.K, GNDI.1, GNDI.P$1, GNDI.P$2, GNDO.1, GNDO.P$1, GNDO.P$2, R1.1, R2.1, R3.1, U1.4 (PGND), U1.8 (SGND), V5.1 (GND)
unnamed: C5.1, R5.2
unnamed: C5.2, D2.K, D3.A
RSET: R2.2, U1.3 (RSET)
SS: C2.1, U1.2 (SS)
SW: D1.A, L1.1, R5.1, U1.5 (SW)
V9.3: C3.1, C4.1, C8.1, D1.K, D4.A, R1.2, R4.2, U1.1 (EN), U1.6 (VDD), V5.3 (VIN)
VIN: C1.1, L1.2, VIN.1, VIN.P$1, VIN.P$2
VNEG: -9V.1, -9V.P$1, -9V.P$2, C6.1, D2.A
VOUT: +9V.1, +9V.P$1, +9V.P$2, D4.K

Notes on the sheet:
R3 set for 9V
-9VDC
+9VDC
Put a trim pot here.
Change to 10uH
Change to 0.5ohm
Higher value 10uF
1n4148 on output to balance neg diode drop.

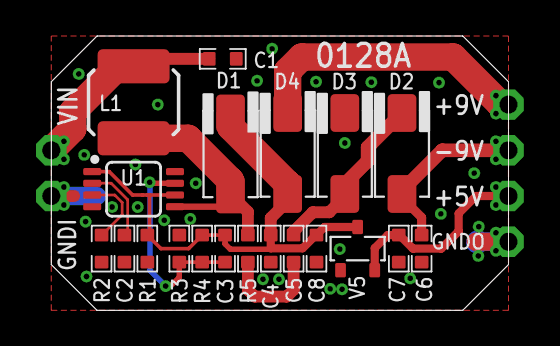
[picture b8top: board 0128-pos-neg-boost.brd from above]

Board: 2 copper layers, 25.4 x 15.2 mm, 26 parts (0 on the bottom side), 12 nets.

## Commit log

2021-02-23 Push the Rev. A boards to GIT hub.
2021-02-23 Update BOM, Schematic, README, 3rd Party PDFs
2021-02-23 Move PCB designs into their proper sub-directories.
2021-02-24 Update Documents
2021-02-24 Rename 0117 Preview images to include revision
2021-02-24 Correct link to preview images
2021-02-28 Rename 0116 to 0116-class-d-amp. Add 3D renders for each CHIP.
2021-02-28 Update how images look on Readme page
2021-03-12 New boards. Created 0119 BOM.
2021-03-12 Update Readme for 0124 and 0125.
2021-03-12 Fix typo in image link.
2021-03-12 3rd Party directory was improperly named.
2021-03-12 Add preview Images for 0124A and 0125A
2021-03-12 Rename preview image to include revision
2021-03-22 Create DESCRIPTION
2021-07-29 CHIPs work in progress
2022-07-02 Made four channel FET for lower power applications.
2022-07-02 Create carrier for 0119 m328p module
2022-07-04 Big batch of new PCBs sent to FAB.
2022-07-06 Retire part number for 0123 test board.
    Probably will never make this board.
2022-07-06 Create 0123 Class-D amp CHIP and carrier board.
2022-07-06 Create 0127 SD-Card CHIP and carrier board.
2022-07-11 Pos/Neg Booster board and carrier
2022-07-11 Added 3D models.
2022-07-18 0129 Codec for MP3/MIDI
2022-07-23 Add 0131 DC Voltage Buck converter
2022-07-23 Update BOM details
2022-07-25 BOM updates
2022-07-25 Create 0131 and carrier
2022-07-25 Create 0132 and carrier
2022-07-29 Updates to library part 0603 resistor
2022-07-29 Updated part from library
2022-07-29 Update C5 value
2022-07-29 Rename new BOM file
2022-07-29 rename BOM file
2022-08-06 BOMs for 0129 and 0229
2022-09-01 Add 8-channel level shifter
2022-09-01 Various updates.
2023-06-19 0234 level shifter carrier PCB
2024-01-31 Created 0135 DCDC pos->neg PCB
2024-02-01 Update Feedback Resistor value.
2024-02-07 Update top-level DESCRIPTION
2025-07-31 Update .gitignore
    Ignore some KiCAD file types.
2025-07-31 Rev B of the #131 DC-DC PCB
2025-07-31 Add #0131-B printed schematic and BOM
2025-07-31 Tune documentation, info block.
2025-07-31 Clean up ignore and CAD pr files.
2025-08-05 Add 3D model to 0131 module.
2025-08-20 Fix part values in schematic.
2025-09-03 Update final parts values.
2025-11-04 Create Synth folder and add Klein VCF design.
2025-11-05 Add README. Some changes related to BOM creation.
2025-11-05 Some changes related to BOM creation settings.
2025-11-05 Create schematic PDF document.
2025-11-05 Changes related to BOM creation settings.
2025-11-05 Add BOMs for Synth CHIPz
2025-11-25 Change recommended pot part values from 10K to 1M.
2025-11-25 Add note regarding faceplate mounts. Bumped Rev. to B.
2025-11-25 Adjust resistor value.
2025-11-25 Correct swapped reference silk for R21,R22. Bump Rev.
2025-11-25 Bump rev to match PCB silk change.
2025-11-25 Add note to highlight swapped resistor value references.
2025-11-26 Create Rev.A of VCA PCB
2025-11-27 Add phantom hookup notes.
2025-11-28 VCF P and N silk were swapped! Fixed.
2025-11-28 Bump Rev to reflect PCB change.
2026-01-14 Add VCA schematic and BOM
2026-01-14 Update KiCAD project settings.
